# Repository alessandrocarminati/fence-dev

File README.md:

# Fence (Poor man's IPMI)

This is the implementation of an IPMI based on ESP6266 WeMos D1 Mini board.
The main requirement is to be cheap.

# Hardware

Here is the list of components:

0. 1 WeMos D1 mini
0. 1 Resistor 220 ohm
0. 1 Resistor 10k ohm
0. 2 4n25 optocoupler
0. 2 1x2 male pin header
0. 1 1x4 male pin header
0. 2 1x8 female pin header
0. 1 Fence board

This is an example of the board needed to have the functionality:

Front view

Back view

The `hw` directory contains the hardware board design file written using kicad.

# Software

The software is a simple Arduino schetch.

Required libraries for build it:

* ESP8266WebServer (https://github.com/codemee/ESP8266WebServer)
* SoftwareSerial (https://github.com/plerup/espsoftwareserial)
* WebSockets (https://github.com/Links2004/arduinoWebSockets)

## Note

HTML pages are gzipped binary blobs included statically as a char array.
To generate them, please execute the `build_header.sh` script before
compiling the schetch using the Arduino ide.

# Known issues

The Wemos D1 mini has the hardware serial used by the USB2Serial device.
For this reason it can not be used to link the controlled device.
To have the serial monitor feature, a software serial is used.
Apparently it can not exceed the 38400 bps, and at that speed, 
sopradic transmission errors can occur.

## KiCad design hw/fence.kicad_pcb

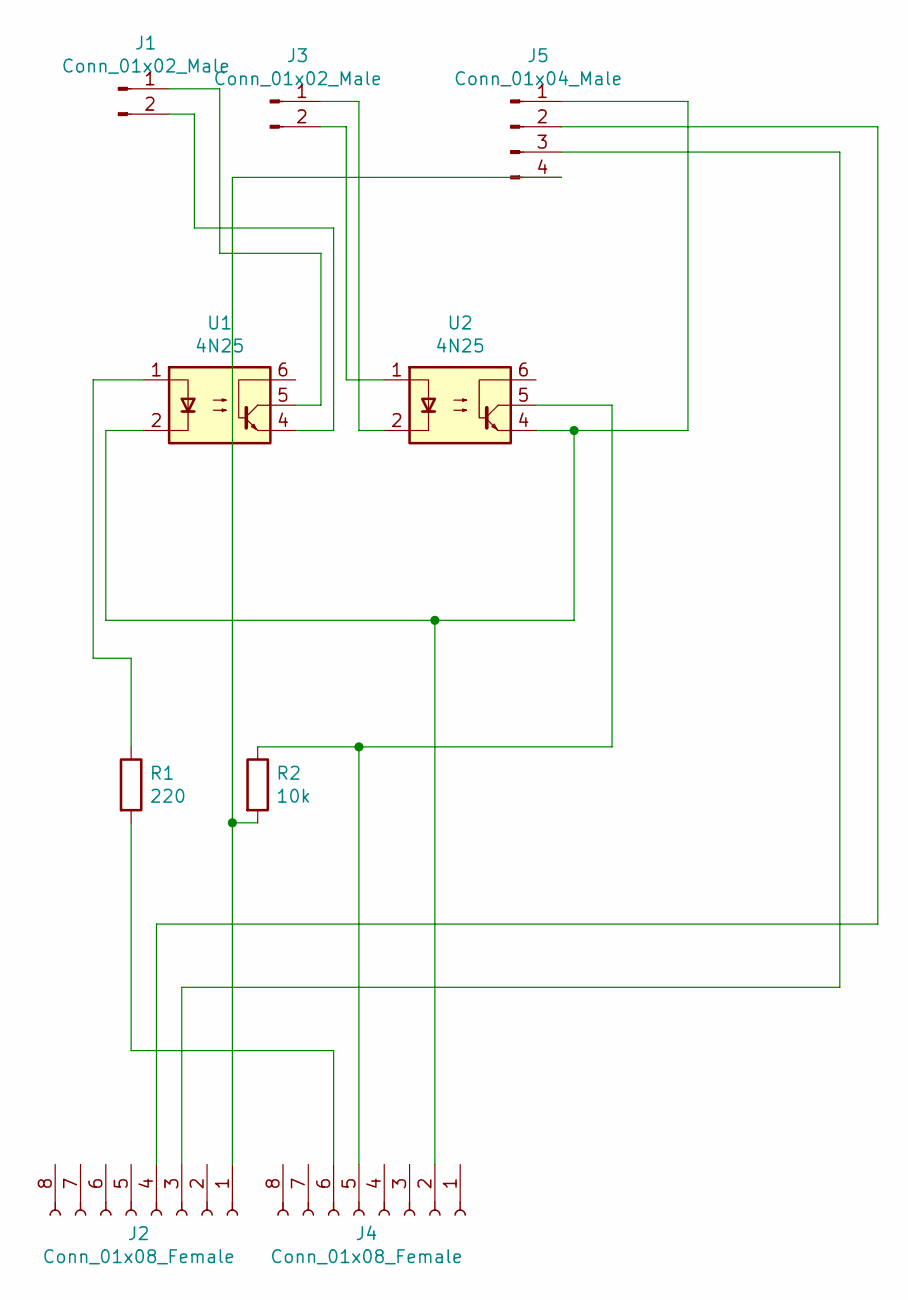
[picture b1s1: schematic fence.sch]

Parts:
J1, J3: Conn_01x02_Male; PinHeader_1x02_P2.54mm_Vertical
J2, J4: Conn_01x08_Female; PinSocket_1x08_P2.54mm_Vertical
J5: Conn_01x04_Male; PinHeader_1x04_P2.54mm_Vertical
R1: 220; R_Axial_DIN0207_L6.3mm_D2.5mm_P10.16mm_Horizontal
R2: 10k; R_Axial_DIN0207_L6.3mm_D2.5mm_P10.16mm_Horizontal
U1, U2: 4N25; DIP-6_W7.62mm

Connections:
unnamed: J1.1, U1.5
unnamed: J1.2, U1.4
unnamed: J2.1, J5.4, R2.2
unnamed: J2.3, J5.3
unnamed: J2.4, J5.2
unnamed: J3.1, U2.2
unnamed: J3.2, U2.1
unnamed: J4.2, J5.1, U1.2, U2.4
unnamed: J4.5, R2.1, U2.5
unnamed: J4.6, R1.2
unnamed: R1.1, U1.1

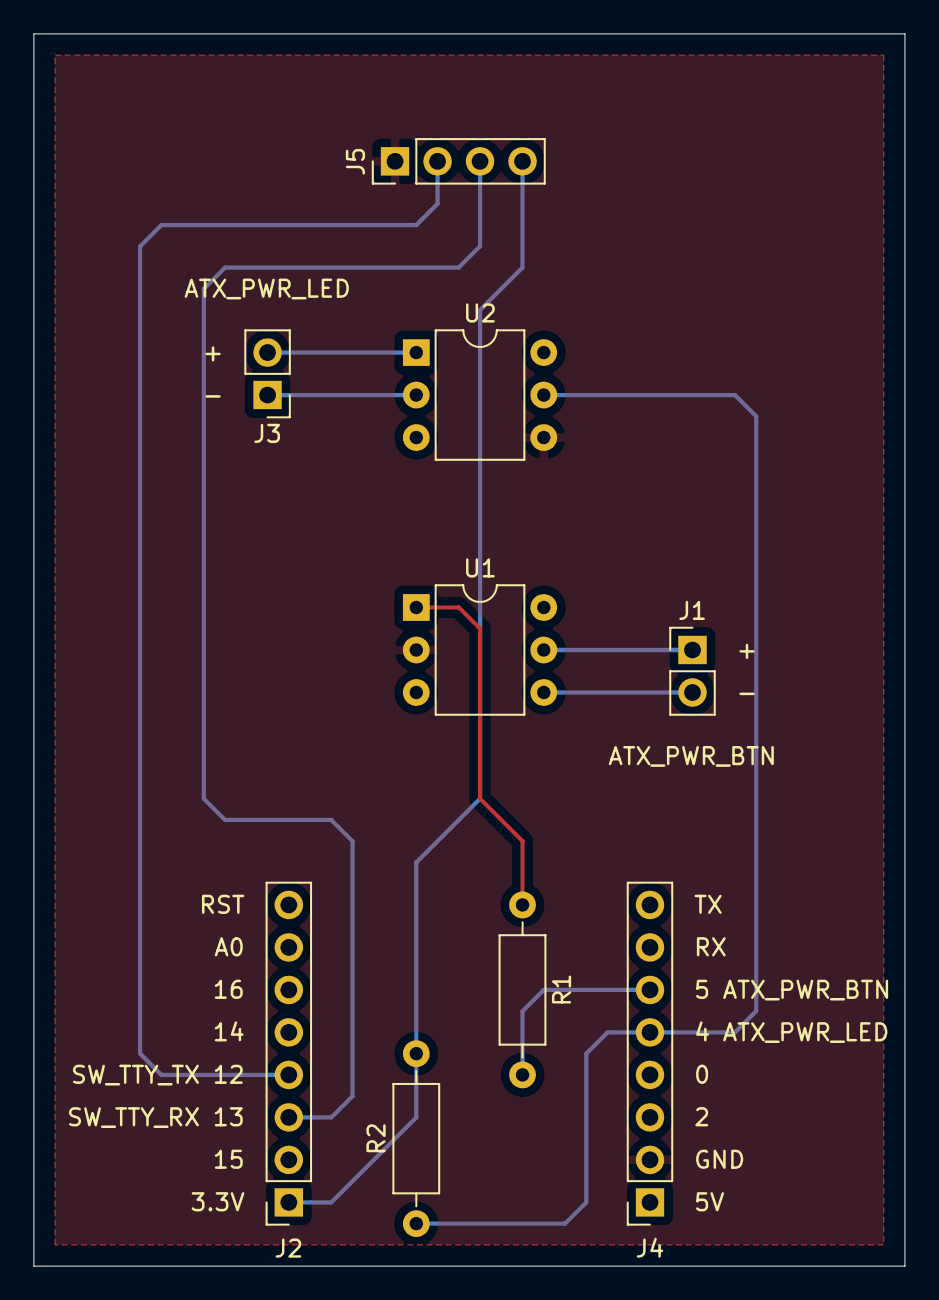
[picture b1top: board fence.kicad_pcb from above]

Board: 2 copper layers, 52.1 x 73.7 mm, 9 parts (0 on the bottom side), 11 nets.

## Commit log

2022-12-31 fix HW: wemos header distance
2022-12-31 Fix: WeMos pin5 leftover
2023-01-03 PCB and hompage updated
2023-01-06 Bundle update
    * pcb refactor & fixes
    * schetch minor cosmethics
    * html buttons rename and synchronization with indicators
2023-01-06 gitignore updated for 2 git in the same dir
